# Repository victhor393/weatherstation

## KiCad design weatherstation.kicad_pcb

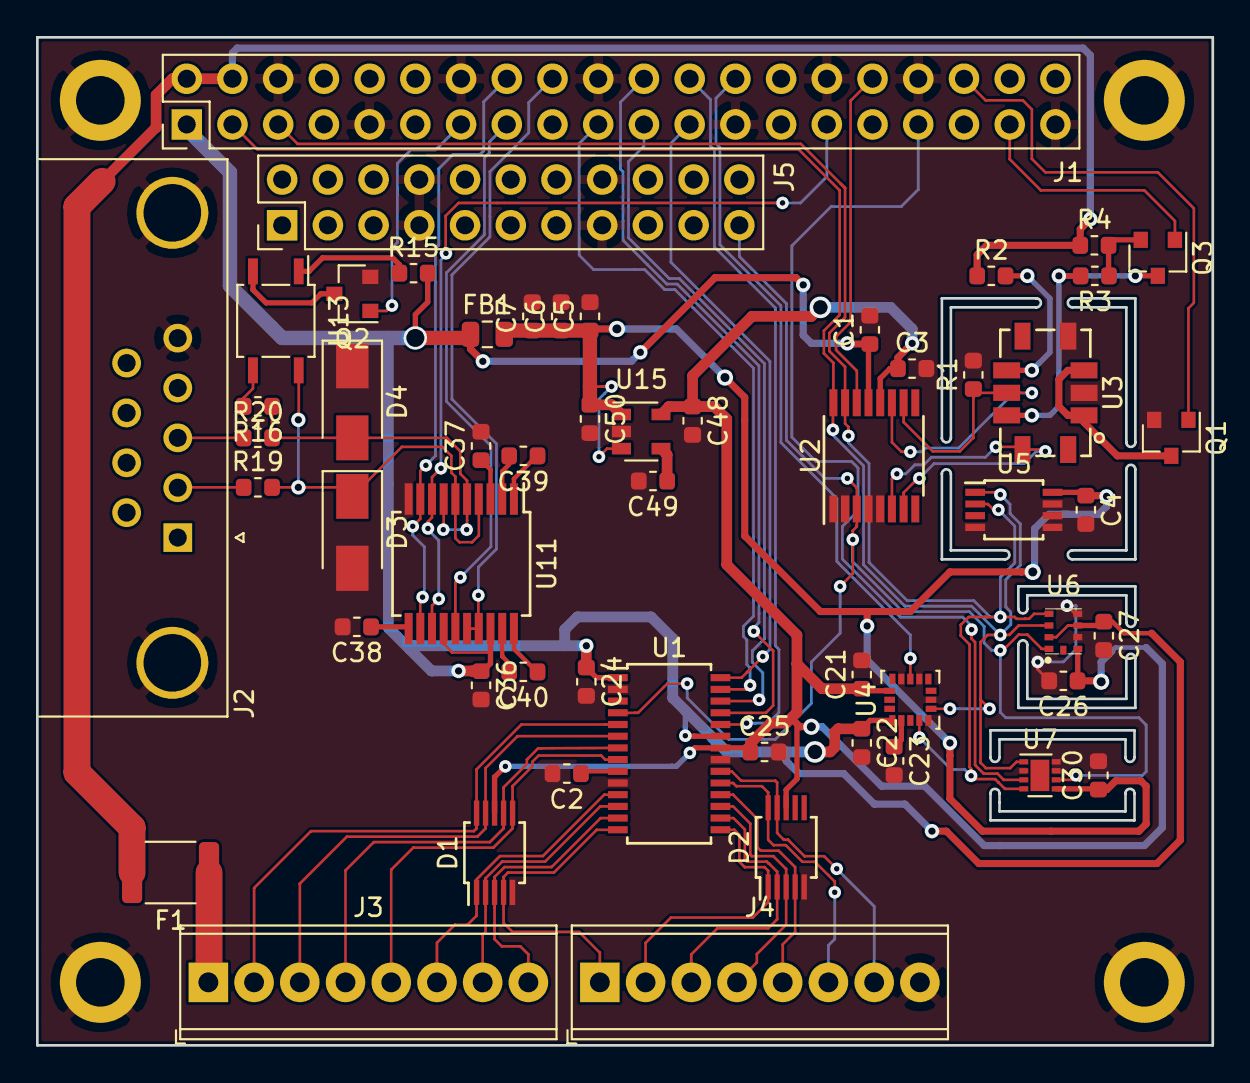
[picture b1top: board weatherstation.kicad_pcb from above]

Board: 2 copper layers, 65.3 x 56.0 mm, 59 parts (0 on the bottom side), 60 nets.

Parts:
C1, C3, C4, C7, C22, C23, C24, C25, C26, C27, C30, C36, C37, C38, C39, C40, C48: 100nF; C_0603_1608Metric
C2, C21: 4.7uF; C_0603_1608Metric
C5, C6: 22uF; C_0603_1608Metric
C49: 10nF; C_0603_1608Metric
C50: 2.2uF; C_0603_1608Metric
D1, D2: CM1213A-08SO; MSOP-10_3x3mm_P0.5mm
D3, D4: WE_824501700; D_SMA
F1: PFMF.030.2; R_1812_4532Metric
FB1: 180R/100M; L_0805_2012Metric
H1, H2, H3, H4: MountingHole_Pad; MountingHole_2.7mm_M2.5_ISO14580_Pad
J1: Conn_02x20_Odd_Even; PinHeader_2x20_P2.54mm_Vertical
J2: DB9_Female_MountingHoles; DSUB-9_Female_Horizontal_P2.77x2.84mm_EdgePinOffset4.94mm_H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
J3, J4: Screw_Terminal_01x08; TerminalBlock_Phoenix_MPT-0,5-8-2.54_1x08_P2.54mm_Horizontal
J5: Conn_02x11_Odd_Even; PinHeader_2x11_P2.54mm_Vertical
Q1, Q2: NX3020NAK; SOT-23
Q3: PMV160UP; SOT-23
R1: 237k 0.1%; R_0603_1608Metric
R2, R4: 82; R_0603_1608Metric
R3: 51; R_0603_1608Metric
R15: 2.1k; R_0603_1608Metric
R16: 113; R_0603_1608Metric
R19, R20: 10; R_0603_1608Metric
U1: ADS1148-PW; TSSOP-28_4.4x9.7mm_P0.65mm
U2: ADS112C04-PW; TSSOP-16_4.4x5mm_P0.65mm
U3: MICS-4514
U4: MMA8451Q; LGA-16_3x3mm_P0.5mm_LayoutBorder3x5y
U5: LM75C; TSSOP-8_3x3mm_P0.65mm
U6: 2SMPB-02E; LGA-9-_2x2.5x0.85mm_P0.65mm_OMRON
U7: SHT3x-DIS; DFN-8-1EP_2x2mm_P0.5mm_EP1.05x1.75mm
U11: ISL3330; SSOP-20_5.3x7.2mm_P0.65mm
U13: CPC1017N; SOP-4_3.8x4.1mm_P2.54mm
U15: TPS793285-EP; SOT-23-5

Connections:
+2V8: C3.1, C21.1, C25.1, C26.1, C48.1, D1.8, D2.8, U1.22, U2.12, U4.14, U6.8, U15.5
+3.3VA: C4.1, C5.1, C6.1, C7.1, C30.1, C50.1, FB1.2, U5.8, U7.5, U15.1, U15.3
+3V3: C1.1, C22.1, C24.1, C27.1, C36.1, FB1.1, J1.1, R15.2, U1.1, U1.23, U2.13, U4.1, U6.2, U6.6, U11.14, U11.18
+5V: F1.2, J1.2, J1.4, R2.1, R4.1
/connectors/RS485_D+_ESD: J2.3, R20.1
/connectors/RS485_D-_ESD: J2.2, R19.1
/sensors/afe/RsOX_Isrc: U2.6, U2.7, U3.J
/sensors/afe/RsRED_Isrc: R1.1, U2.10, U2.11, U3.G
AFE_AIN0: D1.1, J3.6, U1.11
AFE_AIN1: D1.2, J3.7, U1.12
AFE_AIN2: D2.3, J4.4, U1.17
AFE_AIN3: D2.4, J4.5, U1.18
AFE_AIN4: D1.3, J3.8, U1.13
AFE_AIN5: D1.4, J4.1, U1.14
AFE_AIN6: D2.1, J4.2, U1.15
AFE_AIN7: D2.2, J4.3, U1.16
ALERT_HUMID: J1.33, U7.3
COMM_MODE: J1.29, U11.8, U11.13
COMM_RS232_RX_RS485_D+: D4.2, R16.1, R20.2, U11.5, U11.7
COMM_RS232_TX_RS485_D-: D3.1, R19.2, U11.4, U11.6, U13.4
GND: C1.2, C2.2, C3.2, C4.2, C5.2, C6.2, C7.2, C21.2, C22.2, C23.2, C24.2, C25.2, C26.2, C27.2, C30.2, C36.2, C37.2, C38.2, C48.2, C49.2, C50.2, D1.5, D2.5, D3.2, D4.1, H1.1, H2.1, H3.1, H4.1, J1.6, J1.9, J1.14, J1.20, J1.25, J1.30, J1.34, J1.39, J2.0, J2.5, J4.8, J5.7, J5.8, J5.15, J5.16, Q1.2, Q2.2, R1.2, U1.2, U1.10, U1.21, U2.1, U2.2, U2.4, U2.5, U3.B, U3.D, U4.5, U4.7, U4.10, U4.12, U5.4, U5.5, U5.6, U5.7, U6.5, U6.7, U7.2, U7.7, U7.8, U11.10, U15.2
GPIO3_A4: J1.15, U11.15
GPIO3_A5: J1.16, U11.9, U11.12
GPIO3_A6: J1.18, U11.16, U11.17
I2C0_SCL: J1.5, U2.15, U4.4, U5.2, U6.4, U7.4
I2C0_SDA: J1.3, U2.16, U4.6, U5.1, U6.3, U7.1
IEXC1: D2.9, J4.7, U1.20
IEXC2: D2.10, J4.6, U1.19
INT1_ACCEL: J1.26, U4.11
unnamed: C2.1, U1.9
unnamed: C23.1, U4.2
unnamed: C37.1, U11.3
unnamed: C38.1, U11.11
unnamed: C39.1, U11.1
unnamed: C39.2, U11.2
unnamed: C40.1, U11.20
unnamed: C40.2, U11.19
unnamed: C49.1, U15.4
unnamed: F1.1, J3.1
unnamed: Q1.3, U3.A, U3.C
unnamed: Q2.3, U13.2
unnamed: Q3.2, R3.1, R4.2
unnamed: Q3.3, R3.2, U3.H
unnamed: R2.2, U3.F
unnamed: R15.1, U13.1
unnamed: R16.2, U13.3
REFN0: D1.6, J3.5, U1.8
REFN1: D1.9, J3.3, U1.6
REFP0: D1.10, J3.2, U1.5
REFP1: D1.7, J3.4, U1.7
RS485_TERM: J1.13, Q2.1
SNSR_HEAT: J1.36, Q1.1
SPI_CLK_M2: J1.23, U1.28
SPI_CSN0_M2: J1.24, U1.24
SPI_RXD_M2: J1.21, U1.26
SPI_TXD_M2: J1.19, U1.27
~DRDY_SNSR: J1.32, U2.14
~DRDY~_AFE: J1.22, U1.25
~RESET: J5.21, U1.4, U2.3, U6.1, U7.6
~SNSR_HEAT2: J1.37, Q3.1

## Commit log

2020-06-13 Initial version of weather station project
2020-06-13 Initial changes for rock64 version
2020-06-14 Initial schematic work for rock64 version
2020-07-07 Revision A
2020-07-07 Added license file
